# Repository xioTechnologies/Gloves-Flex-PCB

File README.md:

Gloves-Flex-PCB
===============

Flex circuit design to mount [x-OSC](http://www.x-io.co.uk/products/x-osc/) on gloves.  See [post](http://theglovesproject.com/flex-breakout-board/) on gloves project website for more information.

Original deign by [Hannah Perner Wilson](http://www.plusea.at/).

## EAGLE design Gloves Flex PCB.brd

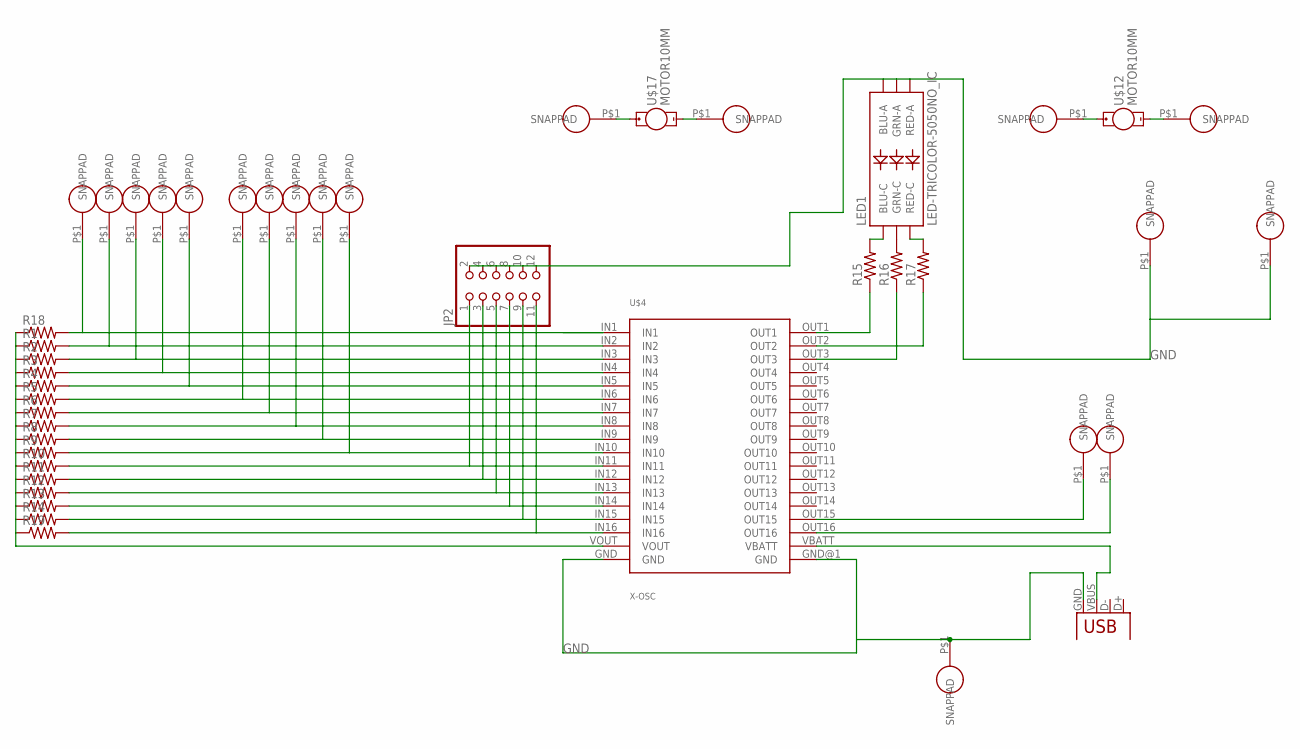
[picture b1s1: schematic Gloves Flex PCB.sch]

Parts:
JP2: PINHD-2X6/90; 2X06/90
LED1: LED-TRICOLOR-5050NO_IC; LED-TRICOLOR-5050
R1, R2, R3, R4, R5, R6, R7, R8, R9, R10, R11, R12, R13, R14, R15, R16, R17, R18, R19: RESISTOR0805-RES; 0805
U$1, U$2, U$3, U$6, U$7, U$8, U$9, U$10, U$11, U$13, U$14, U$15, U$16, U$18, U$19, U$20, U$21, U$22, U$23: SNAP-PAD_7MM_ROUND; SNAP-PAD_7MM_RD
U$4: X-OSC; X-OSC_SMD
U$12, U$17: MOTOR10MM; VIBE-MOTOR-10MM
X1: USB-MICROB

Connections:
GND: JP2.2, JP2.4, JP2.6, JP2.8, JP2.10, JP2.12, LED1.1 (GRN-A), LED1.2 (RED-A), LED1.3 (BLU-A), U$4.GND, U$4.GND@1 (GND), U$15.P$1, U$16.P$1, U$18.P$1, X1.GND
unnamed: LED1.6 (GRN-C), R16.2
unnamed: LED1.4 (BLU-C), R15.2
unnamed: R16.1, U$4.OUT3
unnamed: R1.2, U$1.P$1, U$4.IN2
unnamed: R2.2, U$2.P$1, U$4.IN3
unnamed: R3.2, U$3.P$1, U$4.IN4
unnamed: R4.2, U$4.IN5, U$6.P$1
unnamed: R5.2, U$4.IN6, U$7.P$1
unnamed: R6.2, U$4.IN7, U$8.P$1
unnamed: R7.2, U$4.IN8, U$9.P$1
unnamed: R8.2, U$4.IN9, U$10.P$1
unnamed: R9.2, U$4.IN10, U$11.P$1
unnamed: JP2.1, R10.2, U$4.IN11
unnamed: LED1.5 (RED-C), R17.2
unnamed: JP2.3, R11.2, U$4.IN12
unnamed: JP2.5, R12.2, U$4.IN13
unnamed: JP2.7, R13.2, U$4.IN14
unnamed: JP2.9, R14.2, U$4.IN15
unnamed: JP2.11, R19.2, U$4.IN16
unnamed: U$4.OUT15, U$13.P$1
unnamed: U$4.OUT16, U$14.P$1
unnamed: R17.1, U$4.OUT2
unnamed: R15.1, U$4.OUT1
unnamed: U$12.+, U$22.P$1
unnamed: U$12.-, U$23.P$1
unnamed: U$4.VBATT, X1.VBUS
unnamed: U$17.+, U$19.P$1
unnamed: R18.2, U$4.IN1, U$21.P$1
unnamed: U$17.-, U$20.P$1
unnamed: R1.1, R2.1, R3.1, R4.1, R5.1, R6.1, R7.1, R8.1, R9.1, R10.1, R11.1, R12.1, R13.1, R14.1, R18.1, R19.1, U$4.VOUT

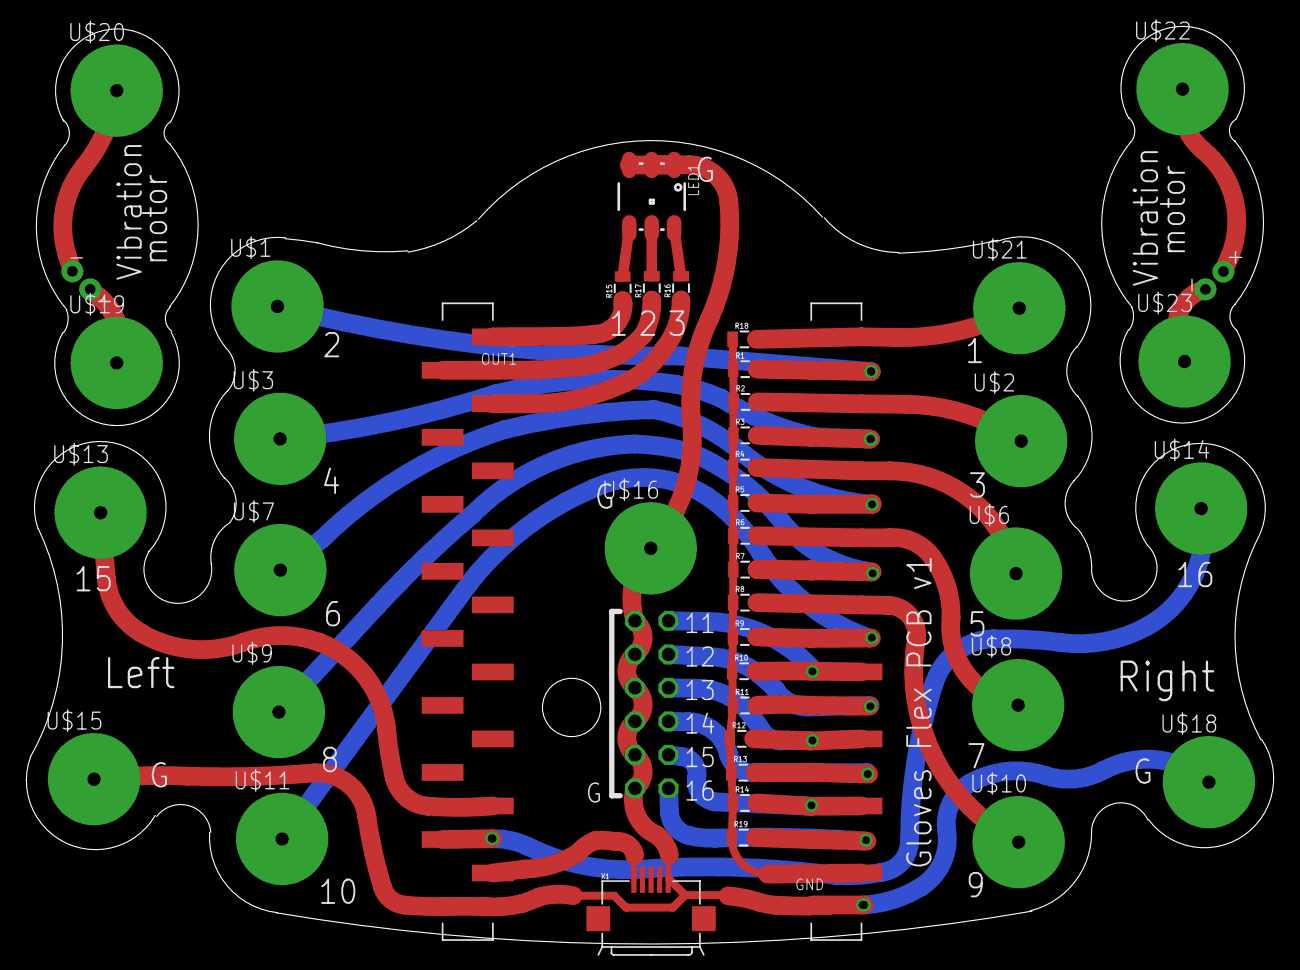
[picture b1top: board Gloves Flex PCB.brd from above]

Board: 2 copper layers, 94.5 x 69.5 mm, 45 parts (1 on the bottom side), 31 nets.

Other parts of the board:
U$5: GLOVES_FLEX_PCB_V1

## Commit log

2014-01-04 Hannah's original design completed in Bristol
2014-01-04 Add .gitignore
2014-01-04 Changes as requested by Hannah from Abu Dhabi
2014-01-04 Include latest hannahsEagleLib.lbr with silkscreen
2014-01-14 Add image of PCB in Eagle
2014-04-10 Add photos
2014-04-10 Correct photo file names

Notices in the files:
parts and their libraries:
SparkFun-Passives: Licensing: CC v3.0 Share-Alike You are welcome to use this library for commercial purposes.
